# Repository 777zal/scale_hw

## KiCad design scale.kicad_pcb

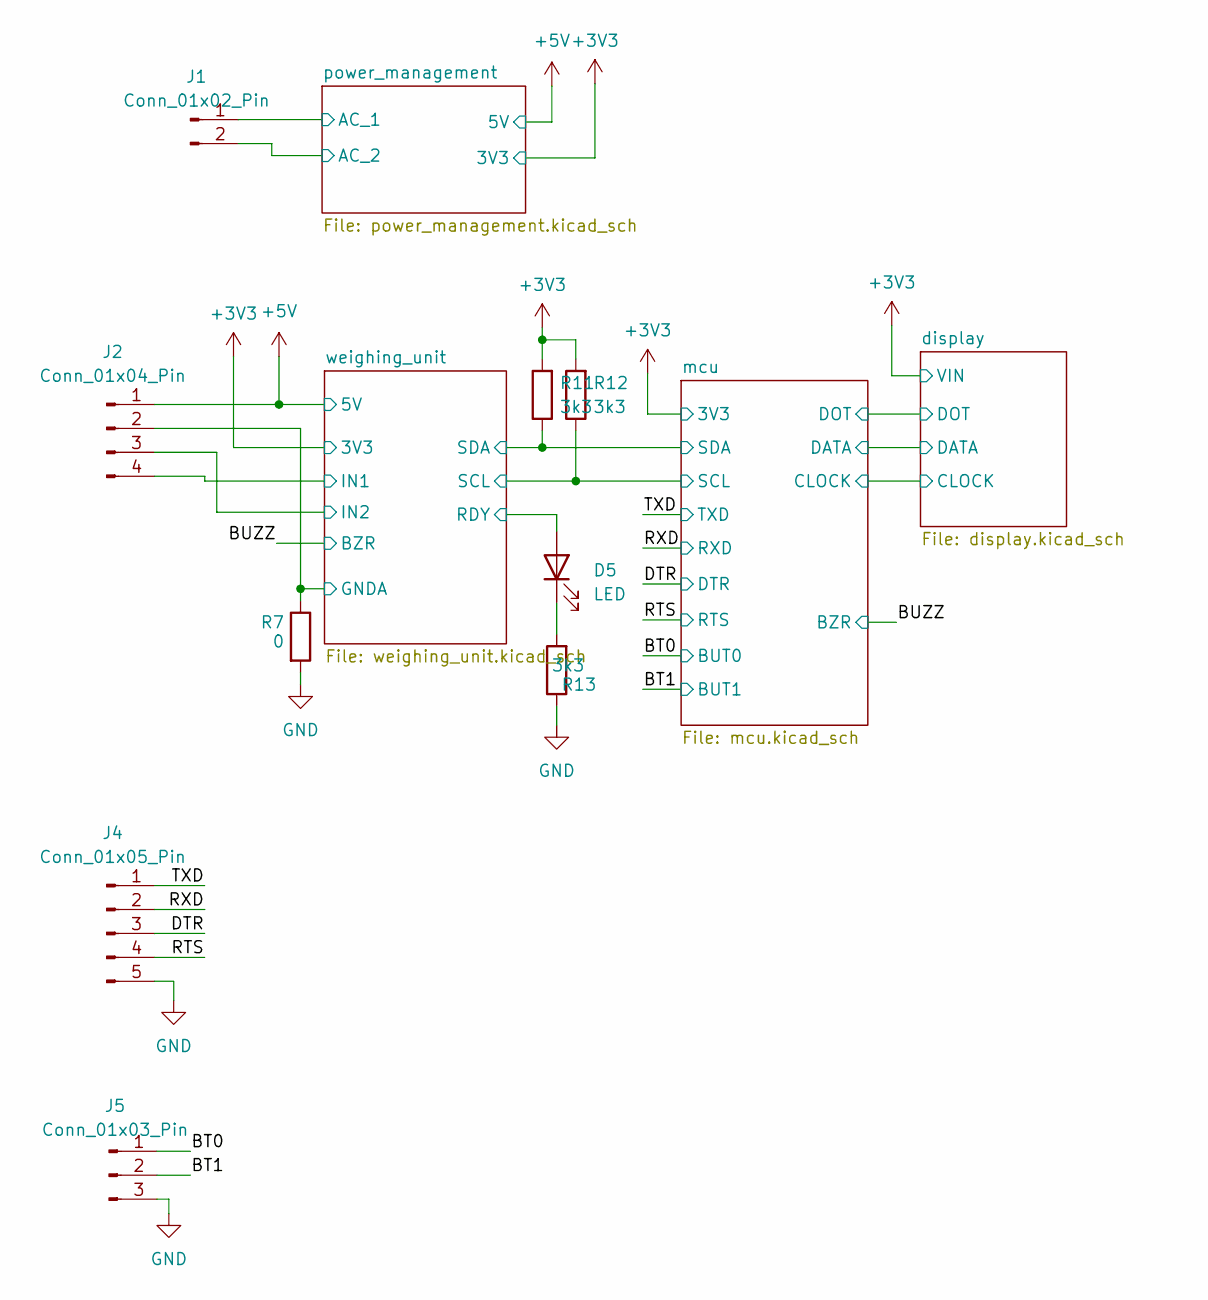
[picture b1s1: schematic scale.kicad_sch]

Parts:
D5: LED; LED_0805_2012Metric
J1: Conn_01x02_Pin; CONN2_284513-2
J2: Conn_01x04_Pin; JST_S4B-XH-A(LF)(SN)
J4: Conn_01x05_Pin; PinHeader_1x05_P2.54mm_Vertical
J5: Conn_01x03_Pin; CONN_S3B-XH-ALFSN_JST
R7: 0; R_0805_2012Metric
R11, R12, R13: 3k3; R_0805_2012Metric

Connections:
+3V3: R11.2, R12.2; also elsewhere on the board
+5V: J2.1; also elsewhere on the board
/BT0: J5.1; also elsewhere on the board
/BT1: J5.2; also elsewhere on the board
/DTR: J4.3; also elsewhere on the board
/RTS: J4.4; also elsewhere on the board
/RXD: J4.2; also elsewhere on the board
/TXD: J4.1; also elsewhere on the board
/mcu/SCL: R12.1; also elsewhere on the board
/mcu/SDA: R11.1; also elsewhere on the board
/power_management/AC_1: J1.1; also elsewhere on the board
/power_management/AC_2: J1.2; also elsewhere on the board
/weighing_unit/IN1: J2.4; also elsewhere on the board
/weighing_unit/IN2: J2.3; also elsewhere on the board
/weighing_unit/RDY: D5.2 (A); also elsewhere on the board
GND: J4.5, J5.3, R7.2, R13.1; also elsewhere on the board
GNDA: J2.2, R7.1; also elsewhere on the board
unnamed: D5.1 (K), R13.2

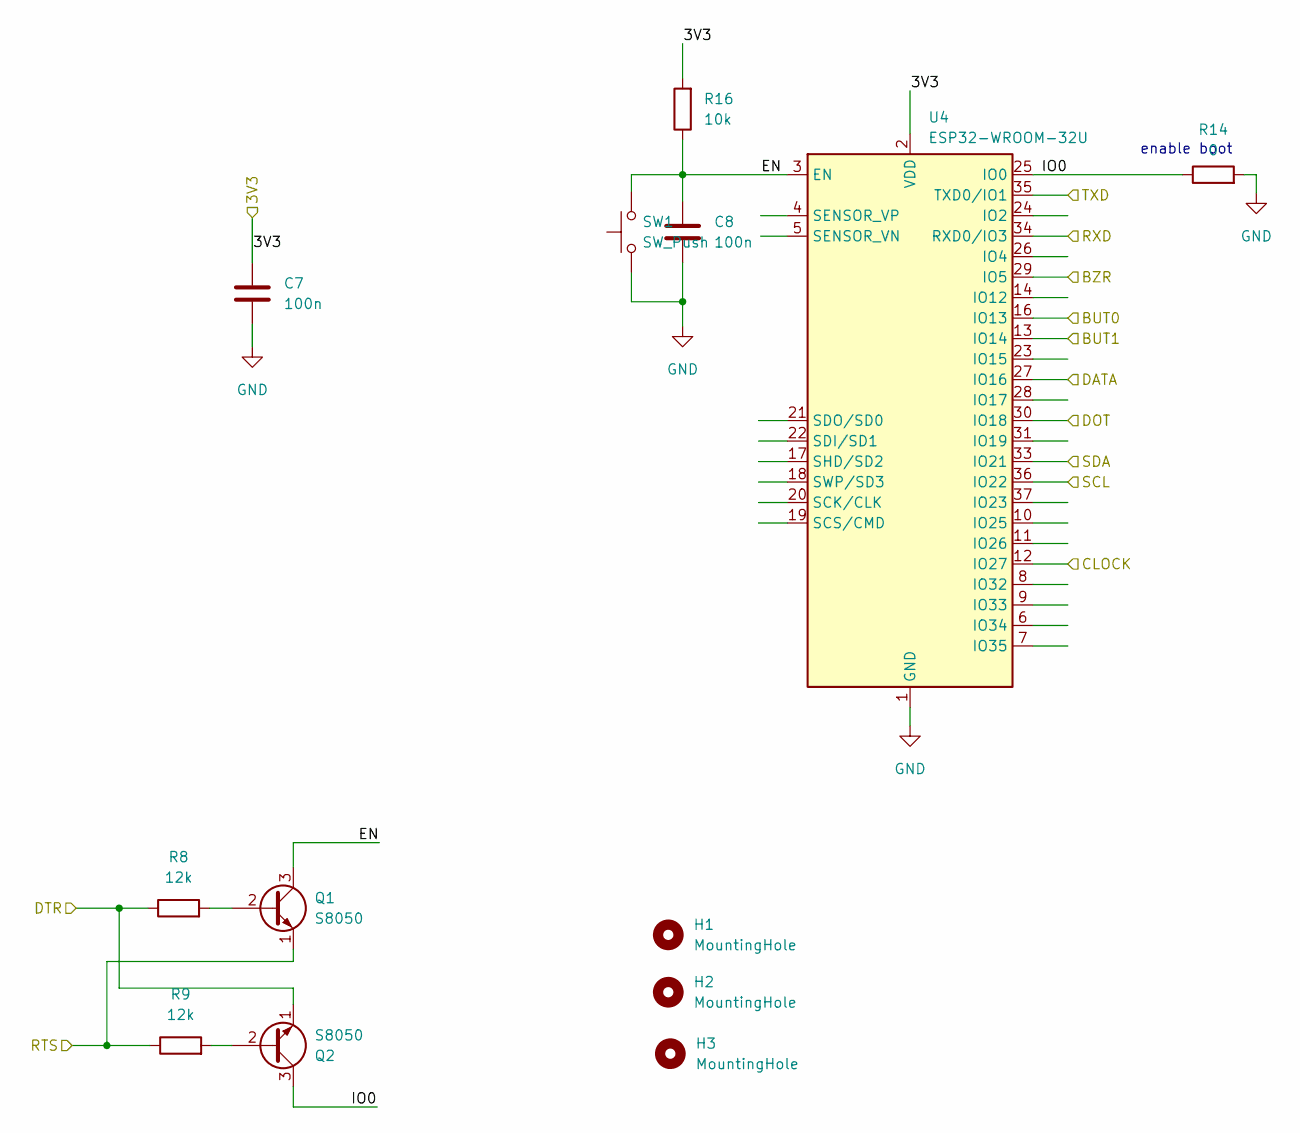
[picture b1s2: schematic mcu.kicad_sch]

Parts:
C7, C8: 100n; C_0805_2012Metric
H1, H2, H3: MountingHole; MountingHole_3mm
Q1, Q2: S8050; SOT-23
R8, R9: 12k; R_0805_2012Metric
R14: 0; R_0805_2012Metric
R16: 10k; R_0805_2012Metric
SW1: SW_Push; SW_DIP_SPSTx01_Slide_6.7x4.1mm_W6.73mm_P2.54mm_LowProfile_J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
U4: ESP32-WROOM-32U

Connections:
+3V3: C7.1, R16.2, U4.2 (VDD); also elsewhere on the board
/BT0: U4.16 (IO13); also elsewhere on the board
/BT1: U4.13 (IO14); also elsewhere on the board
/BUZZ: U4.29 (IO5); also elsewhere on the board
/DTR: Q2.1 (E), R8.1; also elsewhere on the board
/RTS: Q1.1 (E), R9.1; also elsewhere on the board
/RXD: U4.34 (RXD0/IO3); also elsewhere on the board
/TXD: U4.35 (TXD0/IO1); also elsewhere on the board
/display/CLOCK: U4.12 (IO27); also elsewhere on the board
/display/DATA: U4.27 (IO16); also elsewhere on the board
/display/DOT: U4.30 (IO18); also elsewhere on the board
/mcu/EN: C8.1, Q1.3 (C), R16.1, SW1.2, U4.3 (EN)
/mcu/IO0: Q2.3 (C), R14.1, U4.25 (IO0)
/mcu/SCL: U4.36 (IO22); also elsewhere on the board
/mcu/SDA: U4.33 (IO21); also elsewhere on the board
GND: C7.2, C8.2, R14.2, SW1.1, U4.1 (GND), U4.15 (GND), U4.38 (GND), U4.39 (GND); also elsewhere on the board
unnamed: Q1.2 (B), R8.2
unnamed: Q2.2 (B), R9.2

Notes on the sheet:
enable boot

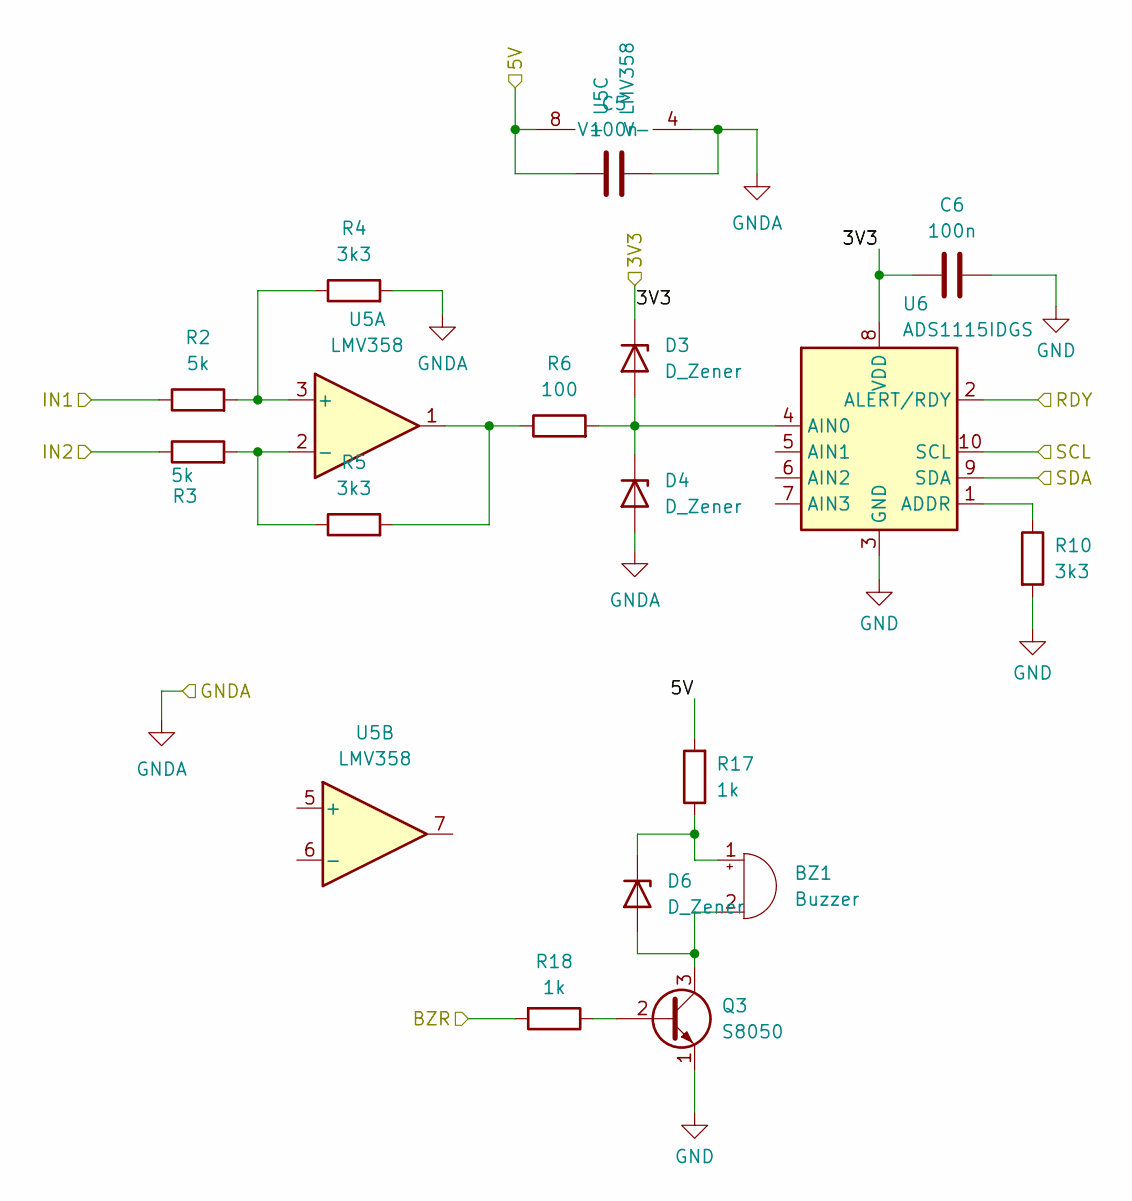
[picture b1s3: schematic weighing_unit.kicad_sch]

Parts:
BZ1: Buzzer; buzz_14mm_CUI_CEP-1162
C5, C6: 100n; C_0805_2012Metric
D3, D4, D6: D_Zener; D_SMA
Q3: S8050; SOT-23
R2, R3: 5k; R_0805_2012Metric
R4, R5, R10: 3k3; R_0805_2012Metric
R6: 100; R_0805_2012Metric
R17, R18: 1k; R_0805_2012Metric
U5: LMV358; SOIC-8_3.9x4.9mm_P1.27mm
U6: ADS1115IDGS; TSSOP-10_3x3mm_P0.5mm

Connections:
+3V3: C6.1, D3.1 (K), U6.8 (VDD); also elsewhere on the board
+5V: C5.1, R17.2, U5.8 (V+); also elsewhere on the board
/BUZZ: R18.2; also elsewhere on the board
/mcu/SCL: U6.10 (SCL); also elsewhere on the board
/mcu/SDA: U6.9 (SDA); also elsewhere on the board
/weighing_unit/IN1: R2.1; also elsewhere on the board
/weighing_unit/IN2: R3.1; also elsewhere on the board
/weighing_unit/RDY: U6.2 (ALERT/RDY); also elsewhere on the board
GND: C6.2, Q3.1 (E), R10.2, U6.3 (GND); also elsewhere on the board
GNDA: C5.2, D4.2 (A), R4.2, U5.4 (V-); also elsewhere on the board
unnamed: BZ1.1 (+), D6.1 (K), R17.1
unnamed: BZ1.2 (-), D6.2 (A), Q3.3 (C)
unnamed: D3.2 (A), D4.1 (K), R6.2, U6.4 (AIN0)
unnamed: Q3.2 (B), R18.1
unnamed: R5.2, R6.1, U5.1
unnamed: R2.2, R4.1, U5.3 (+)
unnamed: R3.2, R5.1, U5.2 (-)
unnamed: R10.1, U6.1 (ADDR)

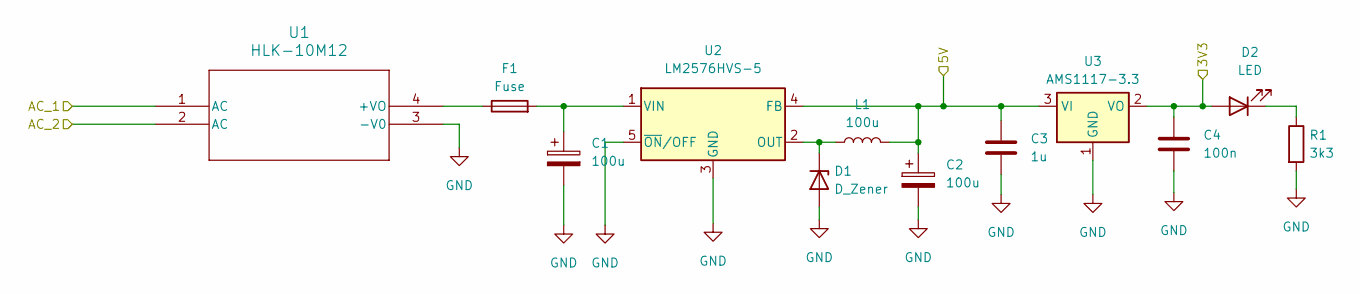
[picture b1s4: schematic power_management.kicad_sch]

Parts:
C1, C2: 100u; CP_Elec_6.3x5.7
C3: 1u; C_0805_2012Metric
C4: 100n; C_0805_2012Metric
D1: D_Zener; D_SMA
D2: LED; LED_0805_2012Metric
F1: Fuse; Fuse_1206_3216Metric
L1: 100u; IND_CDRH127-LDNP-470MC_SUM
R1: 3k3; R_0805_2012Metric
U1: HLK-10M12; HLK-10_HLK
U2: LM2576HVS-5; TO-263-5_TabPin3
U3: AMS1117-3.3; SOT-223-3_TabPin2

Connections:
+3V3: C4.1, D2.2 (A), U3.2 (VO); also elsewhere on the board
+5V: C2.1, C3.1, L1.2, U2.4 (FB), U3.3 (VI); also elsewhere on the board
/power_management/AC_1: U1.1 (AC); also elsewhere on the board
/power_management/AC_2: U1.2 (AC); also elsewhere on the board
GND: C1.2, C2.2, C3.2, C4.2, D1.2 (A), R1.2, U1.3 (-V0), U2.3 (GND), U2.5 (~ON/OFF), U3.1 (GND); also elsewhere on the board
unnamed: D1.1 (K), L1.1, U2.2 (OUT)
unnamed: D2.1 (K), R1.1
unnamed: F1.1, U1.4 (+VO)
unnamed: C1.1, F1.2, U2.1 (VIN)

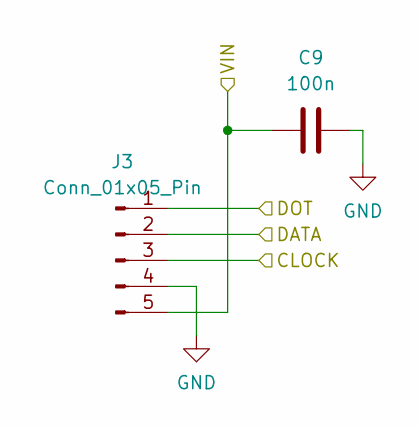
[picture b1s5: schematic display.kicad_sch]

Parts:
C9: 100n; C_0805_2012Metric
J3: Conn_01x05_Pin; JST_S5B-XH-A_LF__SN_

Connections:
+3V3: C9.1, J3.5; also elsewhere on the board
/display/CLOCK: J3.3; also elsewhere on the board
/display/DATA: J3.2; also elsewhere on the board
/display/DOT: J3.1; also elsewhere on the board
GND: C9.2, J3.4; also elsewhere on the board

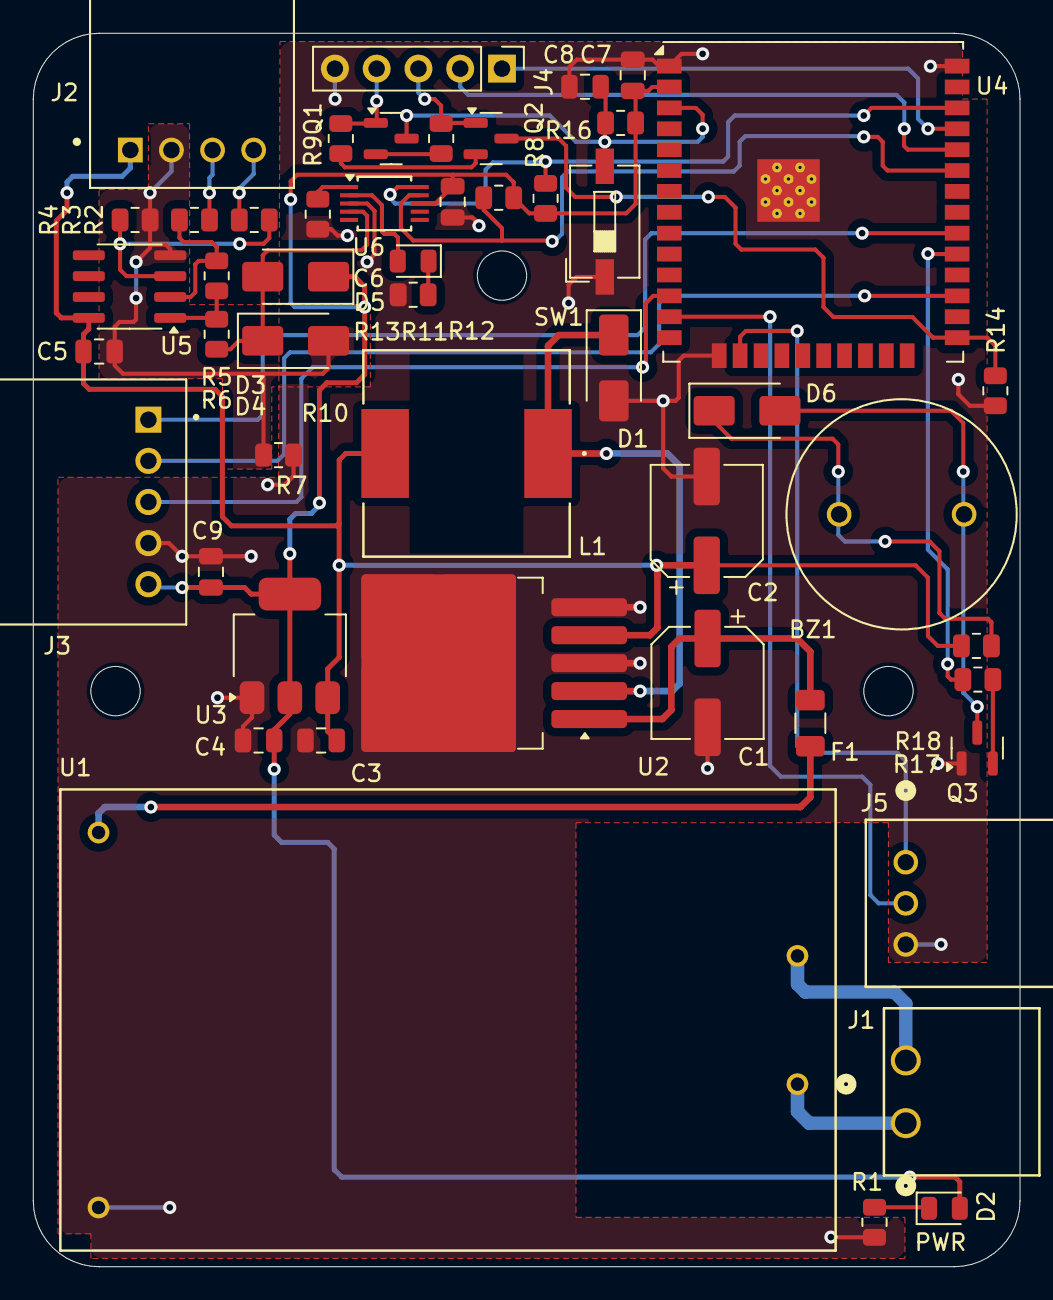
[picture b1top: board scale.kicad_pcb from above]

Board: 4 copper layers, 60.0 x 75.0 mm, 53 parts (0 on the bottom side), 38 nets.

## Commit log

2024-09-02 updated initial commit
2024-09-03 add mcu, sensor, sensor inst, power
2024-09-03 add initial display circuit
2024-09-03 add reset button
2024-09-04 add footprint and step
2024-09-04 edit board file
2024-09-04 routing some signals: I2C, EN, IO0, BUZZ
2024-09-05 update some routings
2024-09-05 completing route 1
2024-09-08 edit copper zone, add pinout address, and reroute EN Signal
2024-09-10 change DATA, BZR, and DOT pins
2024-09-11 edit GND pour generate GBR
2024-09-12 add shell scrip for gerber creation automation
2024-09-13 add script to automate production
2024-09-13 adding project name as gerber file name
2024-09-15 change dimension
2024-10-03 done changes
2024-10-05 start routing
2024-10-05 change dimensions
2024-10-06 done component placement
2024-10-08 finish routing
2024-10-11 add some silkscreen, enable access to BOOT pin
